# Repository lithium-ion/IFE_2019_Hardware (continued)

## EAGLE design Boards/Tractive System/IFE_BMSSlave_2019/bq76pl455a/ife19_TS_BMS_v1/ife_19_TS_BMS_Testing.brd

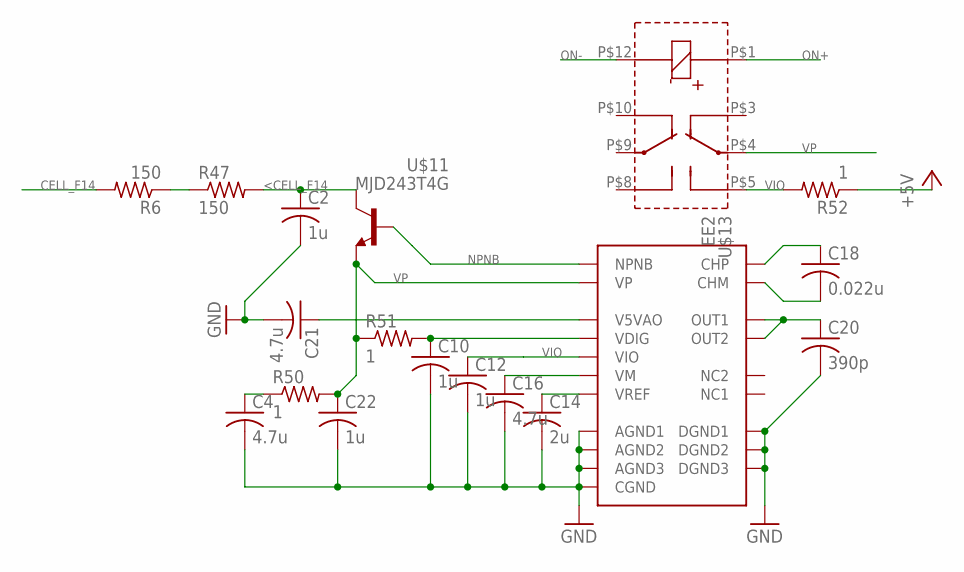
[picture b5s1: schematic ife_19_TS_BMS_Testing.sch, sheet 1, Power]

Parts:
C2, C10, C12, C22: 1u; C0805
C4, C16, C21: 4.7u; C0805
C14: 2u; C0805
C18: 0.022u; C0805
C20: 390p; C0805
R6, R47: 150; R2512
R50, R51, R52: 1; R0805
U$1: BQ76PL455A; TQFP80
U$11: MJD243T4G; TO252
U$13: EE2; EE2-DPDT-SMD

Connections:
<CELL_F14: C2.1, R47.2, U$11.4 (C)
CELL_F14: R6.2; also elsewhere on the board
GND: C2.2, C4.2, C10.2, C12.2, C14.2, C16.2, C20.2, C21.2, C22.2, U$1.30 (DGND1), U$1.35 (DGND2), U$1.37 (DGND3), U$1.48 (CGND), U$1.69 (AGND3), U$1.72 (AGND2), U$1.74 (AGND1); also elsewhere on the board
unnamed: C4.1, R50.1
unnamed: C10.1, R51.2, U$1.34 (VDIG)
unnamed: R52.2, U$13.P$5 ($P5)
unnamed: C14.1, U$1.67 (VREF)
unnamed: C16.1, U$1.31 (VM)
unnamed: C21.1, U$1.58 (V5VAO)
unnamed: R6.1, R47.1
unnamed: C18.1, U$1.32 (CHP)
unnamed: C18.2, U$1.33 (CHM)
unnamed: C20.1, U$1.68 (OUT2), U$1.73 (OUT1)
NPNB: U$1.71 (NPNB), U$11.1 (B)
ON+: U$13.P$1 ($P1); also elsewhere on the board
ON-: U$13.P$12 ($P12); also elsewhere on the board
VIO: C12.1, R52.1, U$1.41 (VIO); also elsewhere on the board
VP: C22.1, R50.2, R51.1, U$1.70 (VP), U$11.3 (E), U$13.P$4 ($P4)

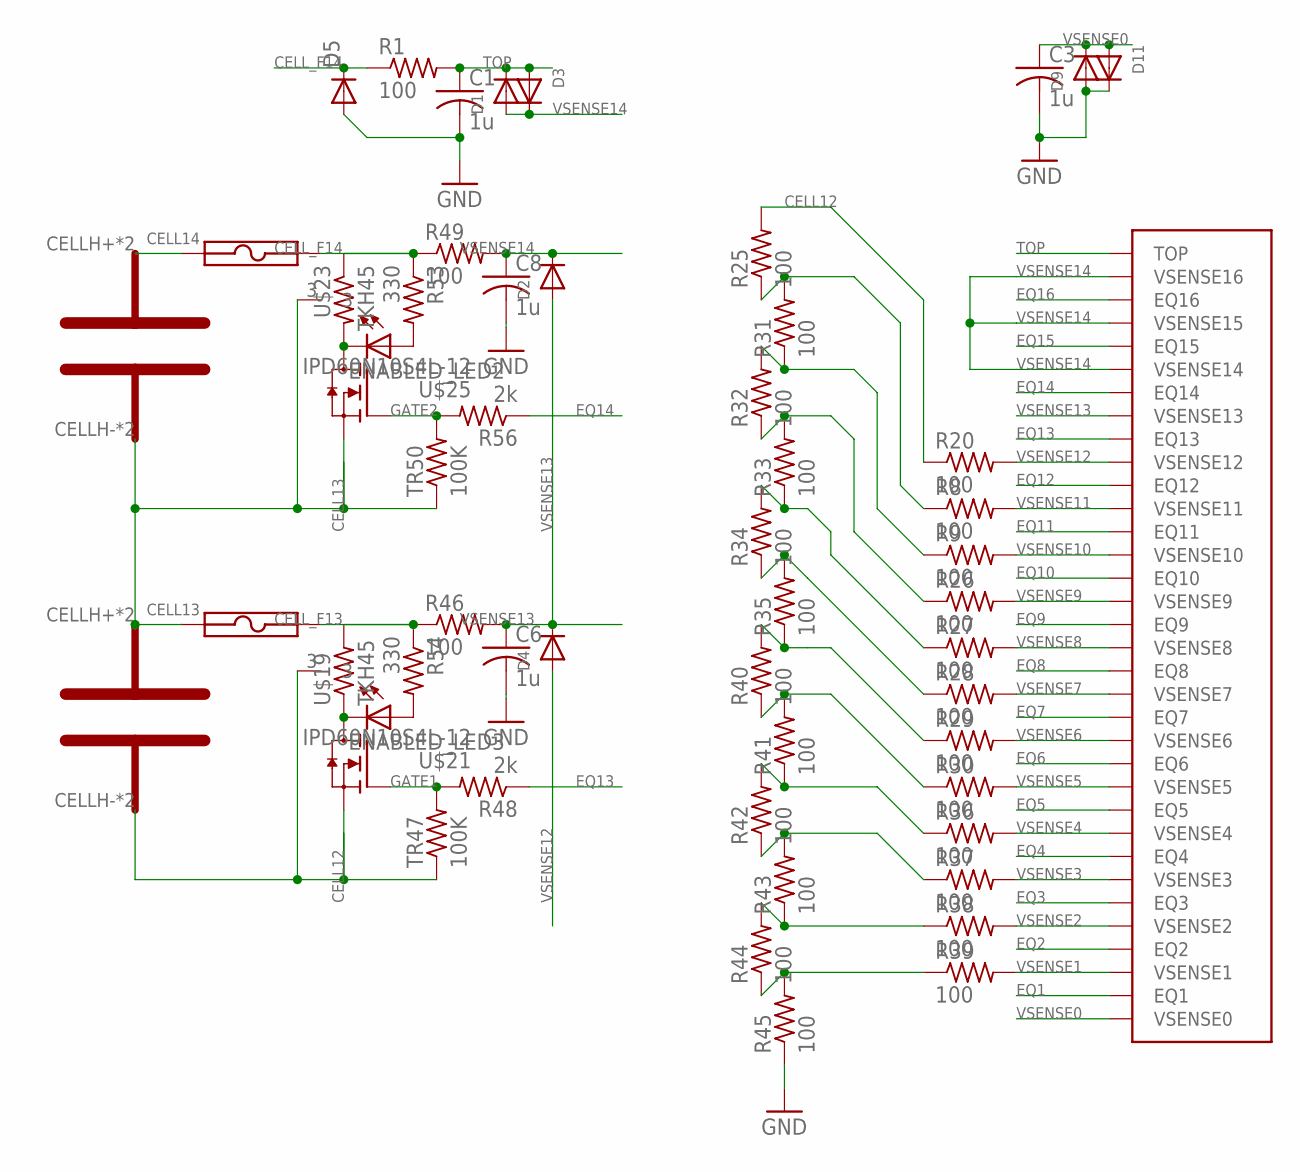
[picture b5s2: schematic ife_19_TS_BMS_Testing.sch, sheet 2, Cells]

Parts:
13, 14: LI6PT; 6PT
C1, C3, C6, C8: 1u; C0603K
D1, D2, D3, D4, D9, D11: DIODESOD-123; SOD-123
D5: DIODE-DO214AC; DO214AC
ENABLED_LED2, ENABLED_LED3: LEDCHIPLED_0603; CHIPLED_0603
R1, R8, R9, R20, R25, R26, R27, R28, R29, R30, R31, R32, R33, R34, R35, R36, R37, R38, R39, R40, R41, R42, R43, R44, R45, R46, R49: 100; R0603
R48, R56: 2k; R0603
R53, R54: 330; R0603
TR47, TR50: 100K; R0603
U$1: BQ76PL455A; TQFP80
U$18, U$22: SF-0603FP; 0603
U$19, U$23: TKH45; TO252-TKH-45
U$21, U$25: IPD60N10S4L-12; TO252

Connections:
CELL12: 13.CELLH- (CELL-), 13.CELLP- (CELL-), R20.1, R25.2, TR47.1, U$19.3, U$21.3 (S); also elsewhere on the board
CELL13: 13.CELLH+ (CELL+), 13.CELLP+ (CELL+), 14.CELLH- (CELL-), 14.CELLP- (CELL-), TR50.1, U$18.1, U$23.3, U$25.3 (S)
CELL14: 14.CELLH+ (CELL+), 14.CELLP+ (CELL+), U$22.1
CELL_F13: R46.1, R54.1, U$18.2, U$19.2; also elsewhere on the board
CELL_F14: D5.C, R1.1, R49.1, R53.1, U$22.2, U$23.1; also elsewhere on the board
EQ1: U$1.28 (EQ1)
EQ2: U$1.26 (EQ2)
EQ3: U$1.24 (EQ3)
EQ4: U$1.22 (EQ4)
EQ5: U$1.20 (EQ5)
EQ6: U$1.18 (EQ6)
EQ7: U$1.16 (EQ7)
EQ8: U$1.14 (EQ8)
EQ9: U$1.12 (EQ9)
EQ10: U$1.10 (EQ10)
EQ11: U$1.8 (EQ11)
EQ12: U$1.6 (EQ12)
EQ13: R48.1, U$1.4 (EQ13)
EQ14: R56.1, U$1.2 (EQ14)
EQ15: U$1.80 (EQ15)
EQ16: U$1.78 (EQ16)
GATE1: R48.2, TR47.2, U$21.1 (G)
GATE2: R56.2, TR50.2, U$25.1 (G)
GND: C1.2, C3.2, C6.2, C8.2, D5.A, D9.A, D11.C, R45.1; also elsewhere on the board
unnamed: ENABLED_LED2.A, R53.2
unnamed: ENABLED_LED3.A, R54.2
unnamed: ENABLED_LED3.C, U$19.1, U$21.2 (D)
unnamed: ENABLED_LED2.C, U$23.2, U$25.2 (D)
unnamed: R8.1, R25.1, R31.2
unnamed: R9.1, R31.1, R32.2
unnamed: R26.1, R32.1, R33.2
unnamed: R27.1, R33.1, R34.2
unnamed: R28.1, R34.1, R35.2
unnamed: R29.1, R35.1, R40.2
unnamed: R30.1, R40.1, R41.2
unnamed: R36.1, R41.1, R42.2
unnamed: R37.1, R42.1, R43.2
unnamed: R38.1, R43.1, R44.2
unnamed: R39.1, R44.1, R45.2
TOP: C1.1, D1.C, D3.A, R1.2, U$1.76 (TOP)
VSENSE0: C3.1, D9.C, D11.A, U$1.29 (VSENSE0)
VSENSE1: R39.2, U$1.27 (VSENSE1)
VSENSE2: R38.2, U$1.25 (VSENSE2)
VSENSE3: R37.2, U$1.23 (VSENSE3)
VSENSE4: R36.2, U$1.21 (VSENSE4)
VSENSE5: R30.2, U$1.19 (VSENSE5)
VSENSE6: R29.2, U$1.17 (VSENSE6)
VSENSE7: R28.2, U$1.15 (VSENSE7)
VSENSE8: R27.2, U$1.13 (VSENSE8)
VSENSE9: R26.2, U$1.11 (VSENSE9)
VSENSE10: R9.2, U$1.9 (VSENSE10)
VSENSE11: R8.2, U$1.7 (VSENSE11)
VSENSE12: D4.A, R20.2, U$1.5 (VSENSE12)
VSENSE13: C6.1, D2.A, D4.C, R46.2, U$1.3 (VSENSE13)
VSENSE14: C8.1, D1.A, D2.C, D3.C, R49.2, U$1.1 (VSENSE14), U$1.77 (VSENSE16), U$1.79 (VSENSE15)

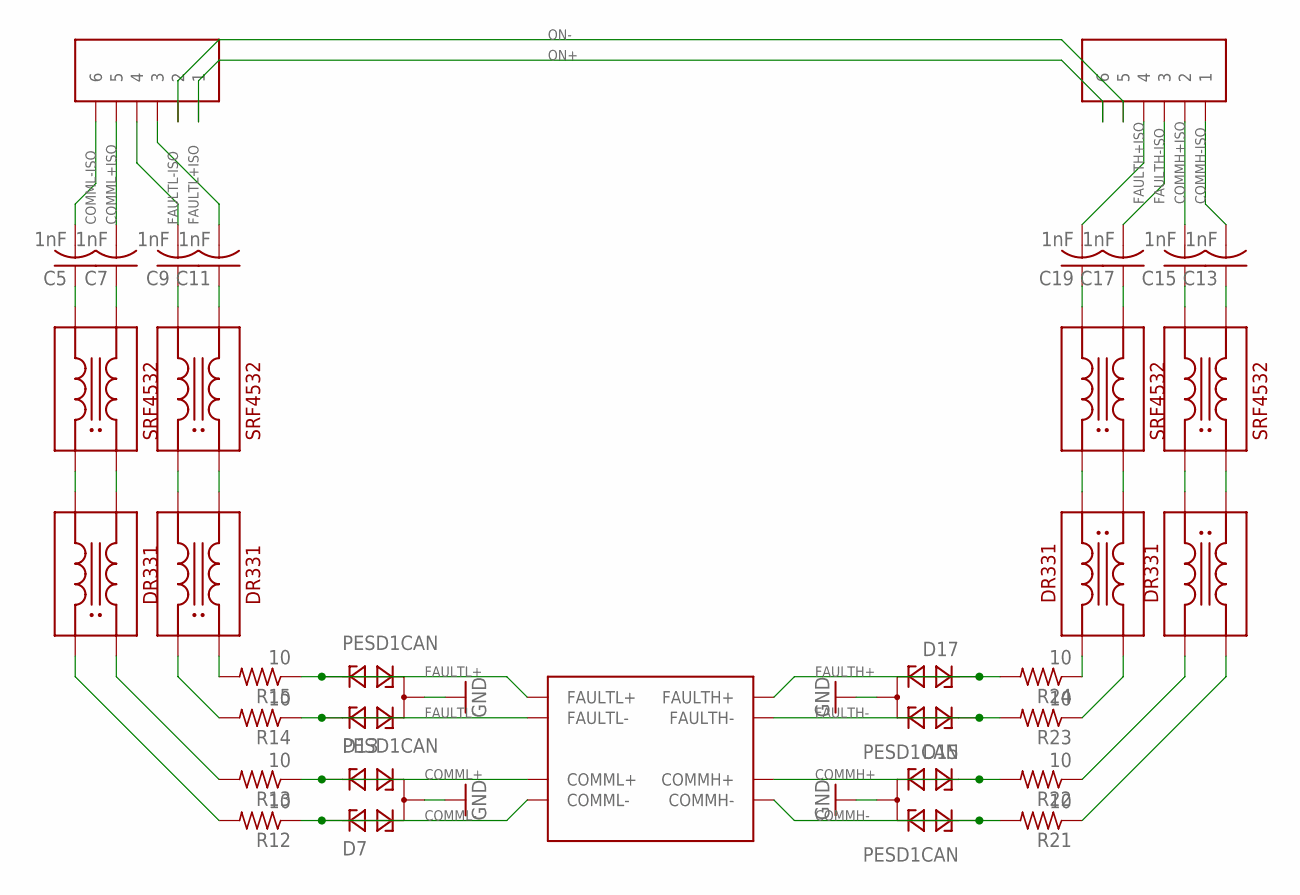
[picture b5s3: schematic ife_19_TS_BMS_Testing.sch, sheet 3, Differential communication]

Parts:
C5, C7, C9, C11, C13, C15, C17, C19: 1nF; C0805
D7, D13, D15, D17: PESD1CAN; SOT23
R12, R13, R14, R15, R21, R22, R23, R24: 10; R0805
U$1: BQ76PL455A; TQFP80
U$2, U$3, U$4, U$6: SRF5432
U$5, U$7: MICROFIT3.0-3P; 6POS-3MM
U$10, U$12, U$14, U$16: DR331

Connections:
COMMH+: D15.1, R22.2, U$1.55 (COMMH+)
COMMH+ISO: C15.2, U$7.P$2 (2)
COMMH-: D15.2, R21.2, U$1.54 (COMMH-)
COMMH-ISO: C13.2, U$7.P$1 (1)
COMML+: D7.2, R13.1, U$1.52 (COMML+)
COMML+ISO: C7.2, U$5.P$5 (5)
COMML-: D7.1, R12.1, U$1.53 (COMML-)
COMML-ISO: C5.2, U$5.P$6 (6)
FAULTH+: D17.1, R24.2, U$1.57 (FAULTH+)
FAULTH+ISO: C19.2, U$7.P$4 (4)
FAULTH-: D17.2, R23.2, U$1.56 (FAULTH-)
FAULTH-ISO: C17.2, U$7.P$3 (3)
FAULTL+: D13.2, R15.1, U$1.50 (FAULTL+)
FAULTL+ISO: C11.2, U$5.P$3 (3)
FAULTL-: D13.1, R14.1, U$1.51 (FAULTL-)
FAULTL-ISO: C9.2, U$5.P$4 (4)
GND: D7.3, D13.3, D15.3, D17.3; also elsewhere on the board
unnamed: C5.1, U$2.P$3 (3)
unnamed: C7.1, U$2.P$2 (2)
unnamed: C9.1, U$3.P$3 (3)
unnamed: C11.1, U$3.P$2 (2)
unnamed: C13.1, U$6.P$2 (2)
unnamed: C15.1, U$6.P$3 (3)
unnamed: C17.1, U$4.P$2 (2)
unnamed: C19.1, U$4.P$3 (3)
unnamed: U$6.P$4 (4), U$14.P$2 (2)
unnamed: U$6.P$1 (1), U$14.P$1 (1)
unnamed: U$4.P$4 (4), U$16.P$2 (2)
unnamed: U$4.P$1 (1), U$16.P$1 (1)
unnamed: U$2.P$1 (1), U$10.P$3 (3)
unnamed: U$2.P$4 (4), U$10.P$4 (4)
unnamed: U$3.P$1 (1), U$12.P$3 (3)
unnamed: U$3.P$4 (4), U$12.P$4 (4)
unnamed: R14.2, U$12.P$1 (1)
unnamed: R13.2, U$10.P$2 (2)
unnamed: R12.2, U$10.P$1 (1)
unnamed: R15.2, U$12.P$2 (2)
unnamed: R23.1, U$16.P$4 (4)
unnamed: R22.1, U$14.P$3 (3)
unnamed: R21.1, U$14.P$4 (4)
unnamed: R24.1, U$16.P$3 (3)
ON+: U$5.P$1 (1), U$7.P$6 (6); also elsewhere on the board
ON-: U$5.P$2 (2), U$7.P$5 (5); also elsewhere on the board

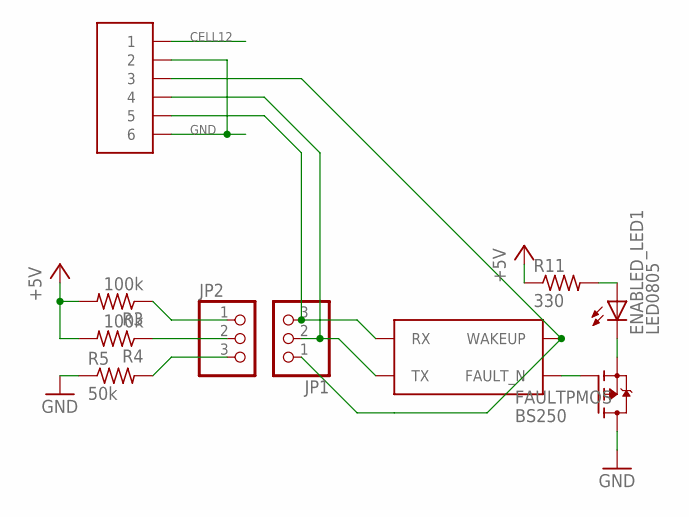
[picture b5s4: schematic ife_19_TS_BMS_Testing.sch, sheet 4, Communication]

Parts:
ENABLED_LED1: LED0805
FAULTPMOS: BS250; SOT23
JP1, JP2: PINHD-1X3CB; 1X03-CLEANBIG
R3, R4: 100k; R0805
R5: 50k; R0805
R11: 330; R0805
U$1: BQ76PL455A; TQFP80
U$9: MICROFIT3.0-3P; 6POS-3MM

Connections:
CELL12: U$9.P$1 (1); also elsewhere on the board
FAULT_N: FAULTPMOS.1 (G), U$1.40 (FAULT_N)
GND: FAULTPMOS.3 (D), R5.1, U$9.P$2 (2), U$9.P$6 (6); also elsewhere on the board
unnamed: ENABLED_LED1.2 (C), FAULTPMOS.2 (S)
unnamed: ENABLED_LED1.1 (A), R11.2
unnamed: JP2.1, R3.1
unnamed: JP1.3, U$1.39 (RX), U$9.P$5 (5)
unnamed: JP2.2, R4.1
unnamed: JP2.3, R5.2
unnamed: JP1.2, U$1.38 (TX), U$9.P$4 (4)
unnamed: JP1.1, U$1.49 (WAKEUP), U$9.P$3 (3)
VIO: R3.2, R4.2, R11.1; also elsewhere on the board

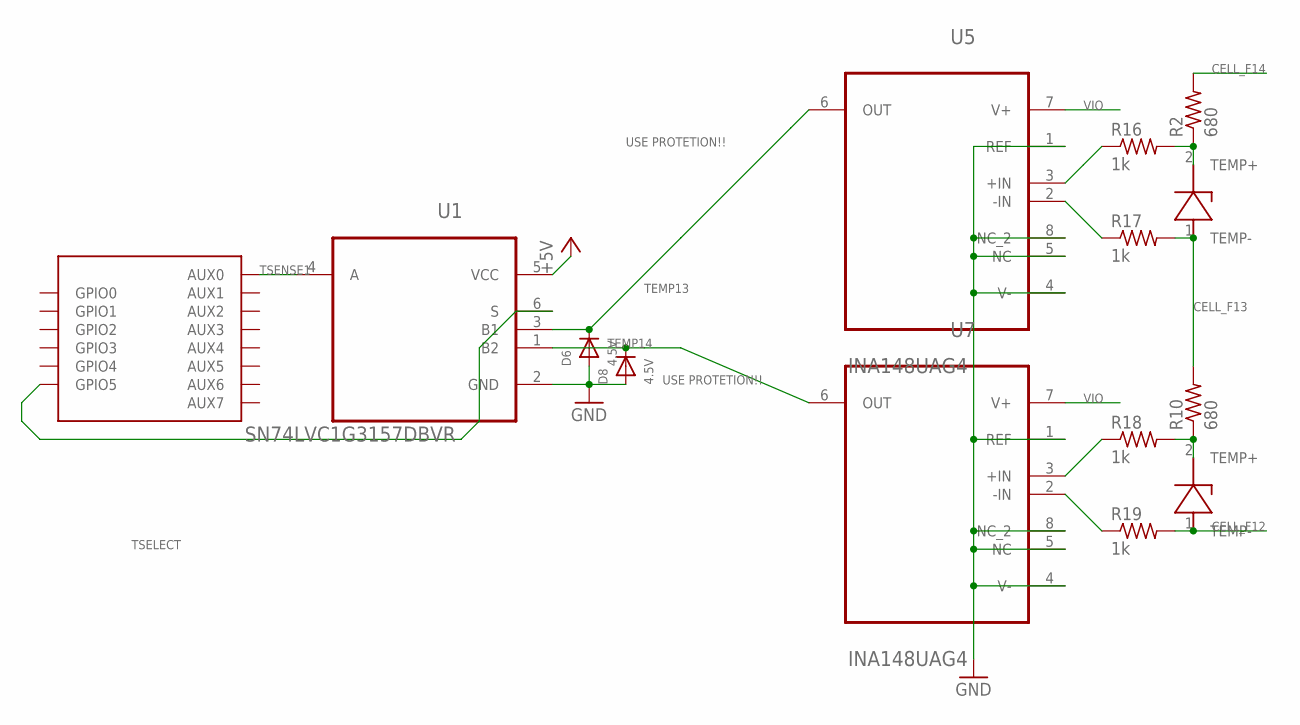
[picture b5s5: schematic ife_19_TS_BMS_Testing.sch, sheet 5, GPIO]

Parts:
13, 14: LI6PT; 6PT
D6, D8: 4.5V; SOD-123
R2, R10: 680; R0603
R16, R17, R18, R19: 1k; R0603
U1: SN74LVC1G3157DBVR; SOT95P280X145-6N
U5, U7: INA148UAG4; SOIC127P600X175-8N
U$1: BQ76PL455A; TQFP80

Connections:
CELL_F12: 13.1 (TEMP-), R19.2
CELL_F13: 14.1 (TEMP-), R10.2, R17.2; also elsewhere on the board
CELL_F14: R2.2; also elsewhere on the board
GND: D6.A, D8.A, U1.2 (GND), U5.1 (REF), U5.4 (V-), U5.5 (NC), U5.8 (NC_2), U7.1 (REF), U7.4 (V-), U7.5 (NC), U7.8 (NC_2); also elsewhere on the board
unnamed: R16.1, U5.3 (+IN)
unnamed: R18.1, U7.3 (+IN)
unnamed: R17.1, U5.2 (-IN)
unnamed: 14.2 (TEMP+), R2.1, R16.2
unnamed: 13.2 (TEMP+), R10.1, R18.2
unnamed: R19.1, U7.2 (-IN)
TEMP13: D6.C, U1.3 (B1), U5.6 (OUT)
TEMP14: D8.C, U1.1 (B2), U7.6 (OUT)
TSELECT: U1.6 (S), U$1.42 (GPIO5)
TSENSE1: U1.4 (A), U$1.66 (AUX0)
VIO: U1.5 (VCC), U5.7 (V+), U7.7 (V+); also elsewhere on the board

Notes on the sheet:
USE PROTETION!!

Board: 4 copper layers, 122 parts (58 on the bottom side), 117 nets, no tracks yet.

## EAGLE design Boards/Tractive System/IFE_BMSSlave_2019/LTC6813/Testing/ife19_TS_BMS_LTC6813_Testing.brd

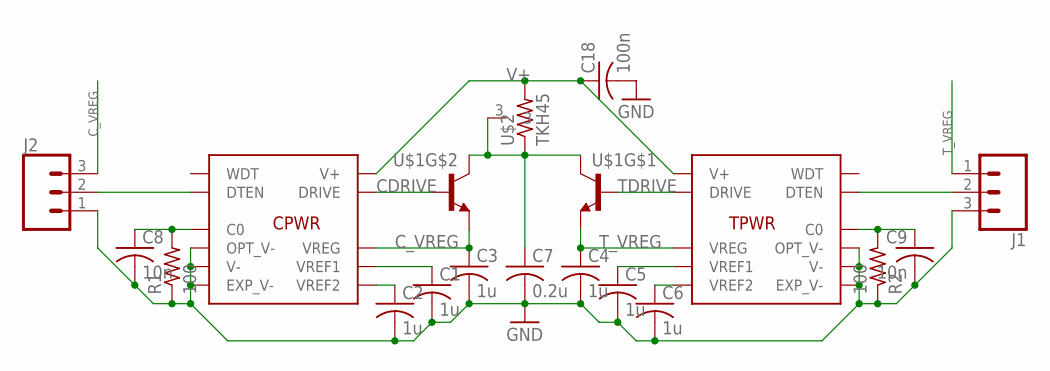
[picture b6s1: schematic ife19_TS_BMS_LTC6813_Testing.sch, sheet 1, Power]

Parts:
C: LTC6813-1; HTQFP-64-EXP
C1, C2, C3, C4, C5, C6: 1u; C0603
C7: 0.2u; C1206
C8, C9: 10n; C0603
C18: 100n; C0603
J1, J2: CONN_03; 1X03
R1, R2: 100; R0603
T: LTC6813-1; HTQFP-64-EXP
U$1: PHPT610030NK; LFPAK56D
U$2: TKH45; TO252-TKH-45

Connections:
CDRIVE: C.49 (DRIVE), U$1.B2 (B)
C_VREG: C.48 (VREG), C3.1, J2.3, U$1.E2 (E); also elsewhere on the board
GND: C.59 (V-), C.60 (OPT_V-), C.65 (EXP_V-), C1.2, C2.2, C3.2, C4.2, C5.2, C6.2, C7.2, C8.2, C9.2, C18.2, J1.3, J2.1, R1.1, R2.1, T.59 (V-), T.60 (OPT_V-), T.65 (EXP_V-); also elsewhere on the board
unnamed: C.51 (VREF1), C1.1
unnamed: C.50 (VREF2), C2.1
unnamed: C5.1, T.51 (VREF1)
unnamed: C6.1, T.50 (VREF2)
unnamed: C.38 (C0), C8.1, R1.2
unnamed: C7.1, U$1.C1 (C), U$1.C2 (C), U$2.1, U$2.3
unnamed: C9.1, R2.2, T.38 (C0)
unnamed: J1.2, T.52 (DTEN)
unnamed: C.52 (DTEN), J2.2
TDRIVE: T.49 (DRIVE), U$1.B1 (B)
T_VREG: C4.1, J1.1, T.48 (VREG), U$1.E1 (E); also elsewhere on the board
V+: C.1 (V+), C18.1, T.1 (V+), U$2.2

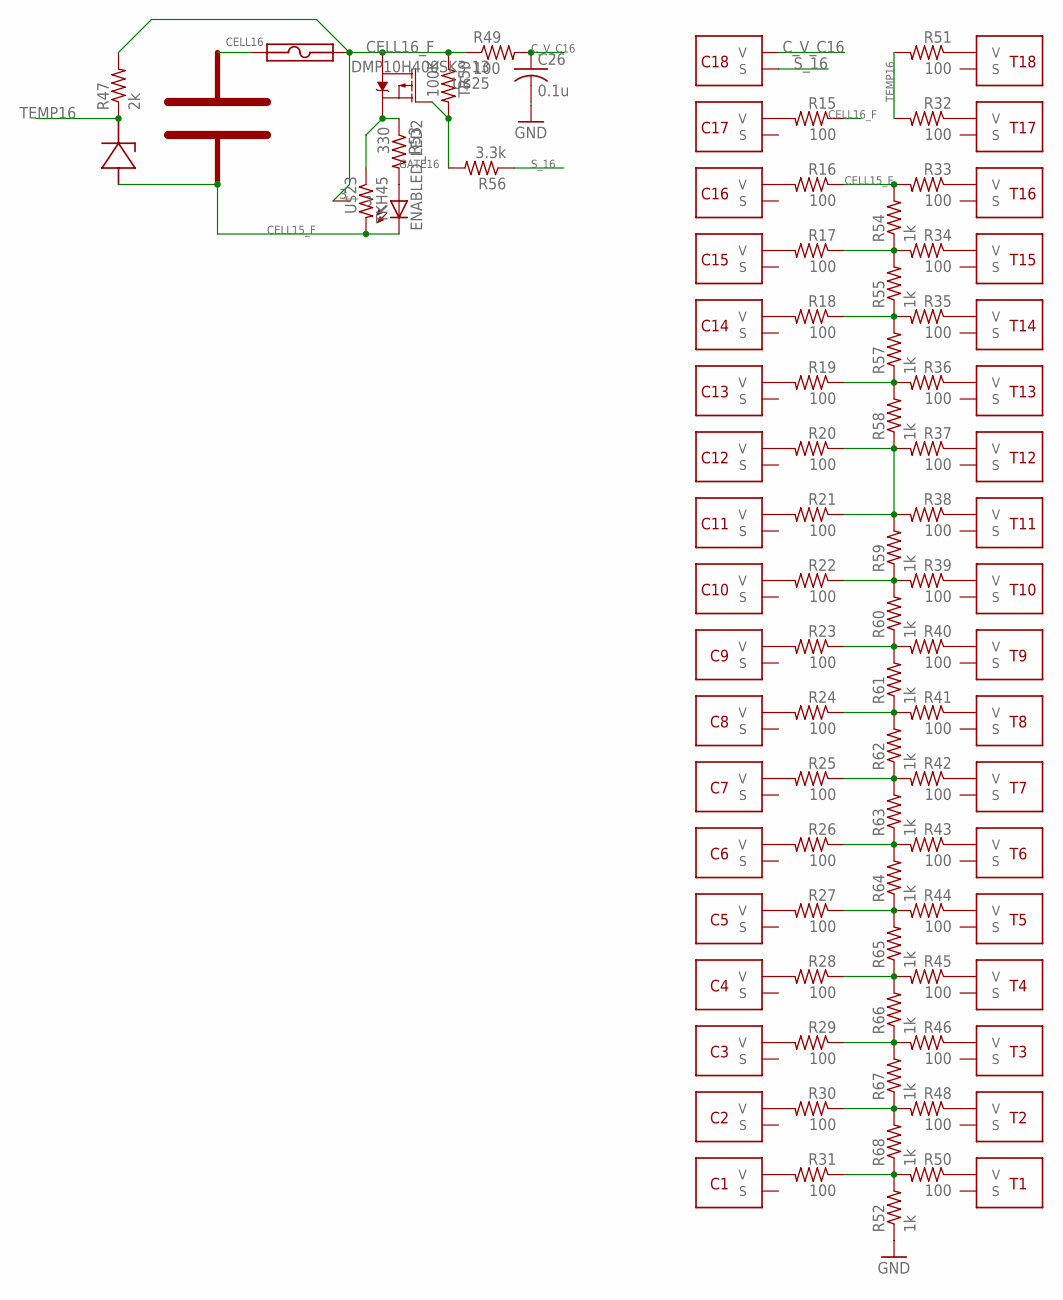
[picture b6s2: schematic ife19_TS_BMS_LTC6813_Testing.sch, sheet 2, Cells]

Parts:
C: LTC6813-1; HTQFP-64-EXP
C26: 0.1u; C0603K
ENABLED_LED2: LEDCHIPLED_0603; CHIPLED_0603
R15, R16, R17, R18, R19, R20, R21, R22, R23, R24, R25, R26, R27, R28, R29, R30, R31, R32, R33, R34, R35, R36, R37, R38, R39, R40, R41, R42, R43, R44, R45, R46, R48, R49, R50, R51: 100; R0603
R47: 2k; R0603
R52, R54, R55, R57, R58, R59, R60, R61, R62, R63, R64, R65, R66, R67, R68: 1k; R0603
R53: 330; R0603
R56: 3.3k; R0603
T: LTC6813-1; HTQFP-64-EXP
TR50: 100K; R0603
U$6: LI6PT; 6PT
U$22: 04661206; R1206W
U$23: TKH45; TO252-TKH-45
U$25: DMP10H400SK3-13; TO252

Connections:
CELL15_F: ENABLED_LED2.C, R16.1, R33.2, R54.2, U$6.1 (TEMP-), U$6.CELLH- (CELL-), U$6.CELLP- (CELL-), U$23.2
CELL16: U$6.CELLH+ (CELL+), U$6.CELLP+ (CELL+), U$22.1
CELL16_F: R15.1, R47.2, R49.1, TR50.1, U$22.2, U$23.3, U$25.2 (D)
C_V_C16: C.2 (V), C26.1, R49.2
GATE16: R56.2, TR50.2, U$25.1 (G)
GND: C26.2, R52.1; also elsewhere on the board
unnamed: ENABLED_LED2.A, R53.2
unnamed: C.4 (V), R15.2
unnamed: C.6 (V), R16.2
unnamed: C.8 (V), R17.2
unnamed: C.10 (V), R18.2
unnamed: C.12 (V), R19.2
unnamed: C.14 (V), R20.2
unnamed: C.16 (V), R21.2
unnamed: C.18 (V), R22.2
unnamed: C.20 (V), R23.2
unnamed: C.22 (V), R24.2
unnamed: C.24 (V), R25.2
unnamed: C.26 (V), R26.2
unnamed: C.28 (V), R27.2
unnamed: C.30 (V), R28.2
unnamed: C.32 (V), R29.2
unnamed: C.34 (V), R30.2
unnamed: C.36 (V), R31.2
unnamed: R32.1, T.4 (V)
unnamed: R33.1, T.6 (V)
unnamed: R34.1, T.8 (V)
unnamed: R35.1, T.10 (V)
unnamed: R36.1, T.12 (V)
unnamed: R37.1, T.14 (V)
unnamed: R38.1, T.16 (V)
unnamed: R39.1, T.18 (V)
unnamed: R40.1, T.20 (V)
unnamed: R41.1, T.22 (V)
unnamed: R42.1, T.24 (V)
unnamed: R43.1, T.26 (V)
unnamed: R44.1, T.28 (V)
unnamed: R45.1, T.30 (V)
unnamed: R46.1, T.32 (V)
unnamed: R48.1, T.34 (V)
unnamed: R50.1, T.36 (V)
unnamed: R51.1, T.2 (V)
unnamed: R20.1, R21.1, R37.2, R38.2, R58.1, R59.2
unnamed: R17.1, R34.2, R54.1, R55.2
unnamed: R18.1, R35.2, R55.1, R57.2
unnamed: R19.1, R36.2, R57.1, R58.2
unnamed: R22.1, R39.2, R59.1, R60.2
unnamed: R23.1, R40.2, R60.1, R61.2
unnamed: R24.1, R41.2, R61.1, R62.2
unnamed: R25.1, R42.2, R62.1, R63.2
unnamed: R26.1, R43.2, R63.1, R64.2
unnamed: R27.1, R44.2, R64.1, R65.2
unnamed: R28.1, R45.2, R65.1, R66.2
unnamed: R29.1, R46.2, R66.1, R67.2
unnamed: R30.1, R48.2, R67.1, R68.2
unnamed: R31.1, R50.2, R52.2, R68.1
unnamed: R53.1, U$23.1, U$25.3 (S)
S_16: C.3 (S), R56.1
TEMP16: R32.2, R47.1, R51.2, U$6.2 (TEMP+)

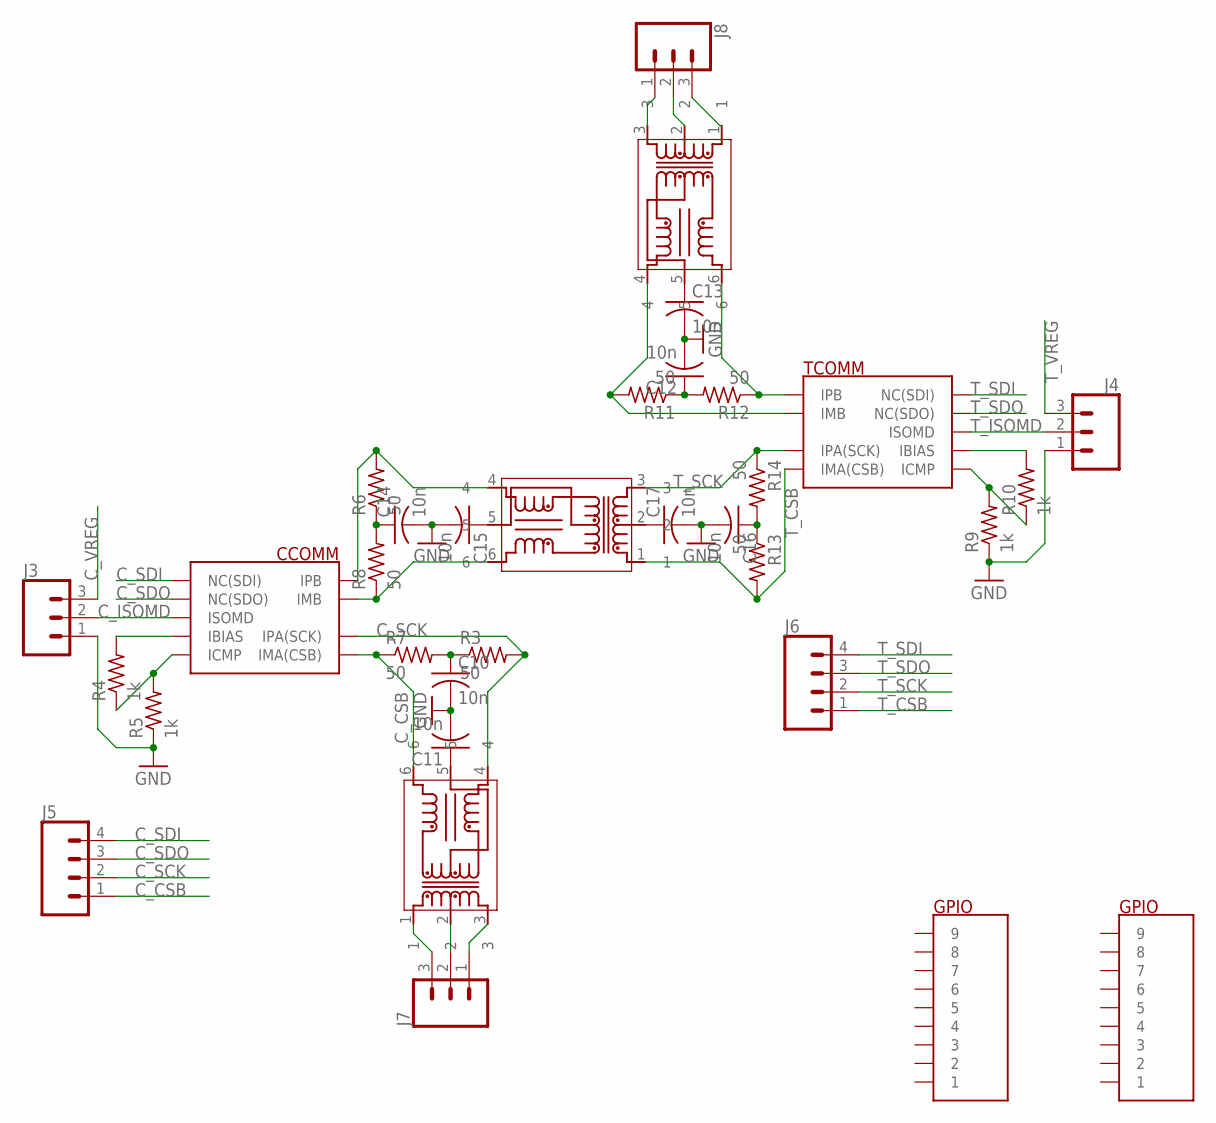
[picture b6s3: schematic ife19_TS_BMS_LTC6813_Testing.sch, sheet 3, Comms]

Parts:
C: LTC6813-1; HTQFP-64-EXP
C10, C11, C12, C13, C14, C15, C16, C17: 10n; C0603K
J3, J4, J7, J8: CONN_03; 1X03
J5, J6: CONN_04; 1X04
R3, R6, R7, R8, R11, R12, R13, R14: 50; R0603
R4, R5, R9, R10: 1k; R0603
T: LTC6813-1; HTQFP-64-EXP
U$3, U$4, U$5: HM2108NL

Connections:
C_CSB: C.61 (IMA(CSB)), J5.1, R7.1, U$3.6
C_ISOMD: C.55 (ISOMD), J3.2
C_SCK: C.62 (IPA(SCK)), J5.2, R3.2, U$3.4
C_SDI: C.53 (NC(SDI)), J5.4
C_SDO: C.54 (NC(SDO)), J5.3
C_VREG: J3.3; also elsewhere on the board
GND: C10.2, C11.2, C12.2, C13.2, C14.2, C15.2, C16.2, C17.2, J3.1, J4.1, R5.1, R9.1; also elsewhere on the board
unnamed: C.58 (ICMP), R4.1, R5.2
unnamed: C.57 (IBIAS), R4.2
unnamed: R10.2, T.57 (IBIAS)
unnamed: R9.2, R10.1, T.58 (ICMP)
unnamed: C10.1, R3.1, R7.2
unnamed: C11.1, U$3.5
unnamed: C12.1, R11.1, R12.2
unnamed: C13.1, U$4.5
unnamed: R11.2, T.63 (IMB), U$4.4
unnamed: R12.1, T.64 (IPB), U$4.6
unnamed: C14.1, R6.1, R8.2
unnamed: C15.1, U$5.5
unnamed: C.64 (IPB), R6.2, U$5.4
unnamed: C.63 (IMB), R8.1, U$5.6
unnamed: C16.1, R13.1, R14.2
unnamed: C17.1, U$5.2
unnamed: J8.1, U$4.3
unnamed: J8.2, U$4.2
unnamed: J8.3, U$4.1
unnamed: J7.2, U$3.2
unnamed: J7.3, U$3.1
unnamed: J7.1, U$3.3
T_CSB: J6.1, R13.2, T.61 (IMA(CSB)), U$5.1
T_ISOMD: J4.2, T.55 (ISOMD)
T_SCK: J6.2, R14.1, T.62 (IPA(SCK)), U$5.3
T_SDI: J6.4, T.53 (NC(SDI))
T_SDO: J6.3, T.54 (NC(SDO))
T_VREG: J4.3; also elsewhere on the board

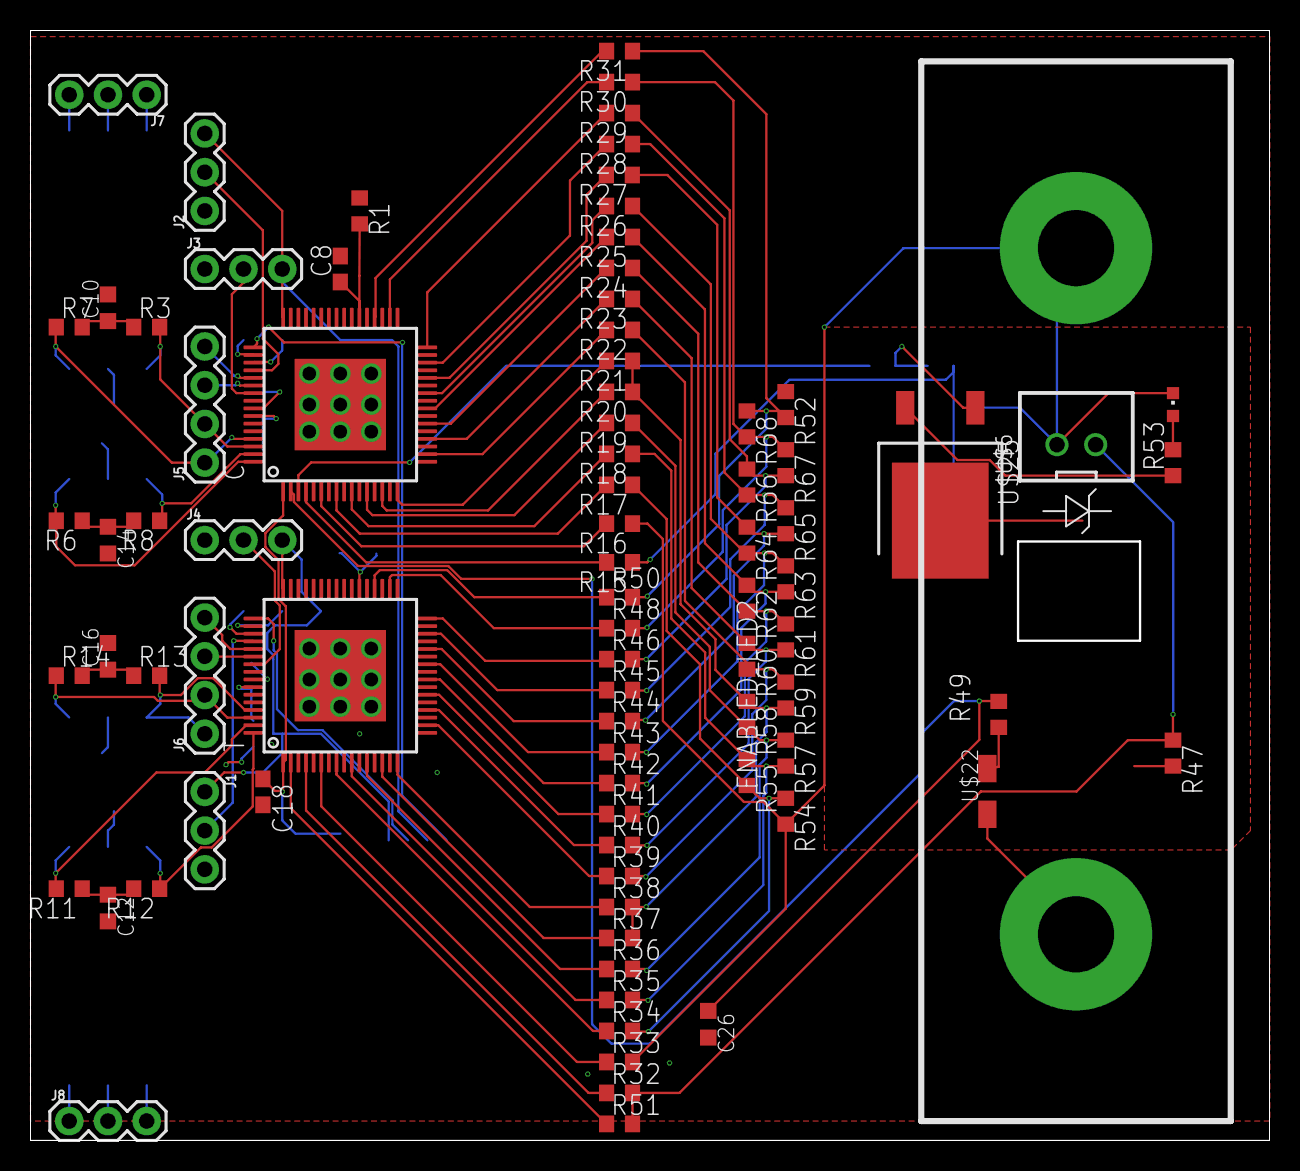
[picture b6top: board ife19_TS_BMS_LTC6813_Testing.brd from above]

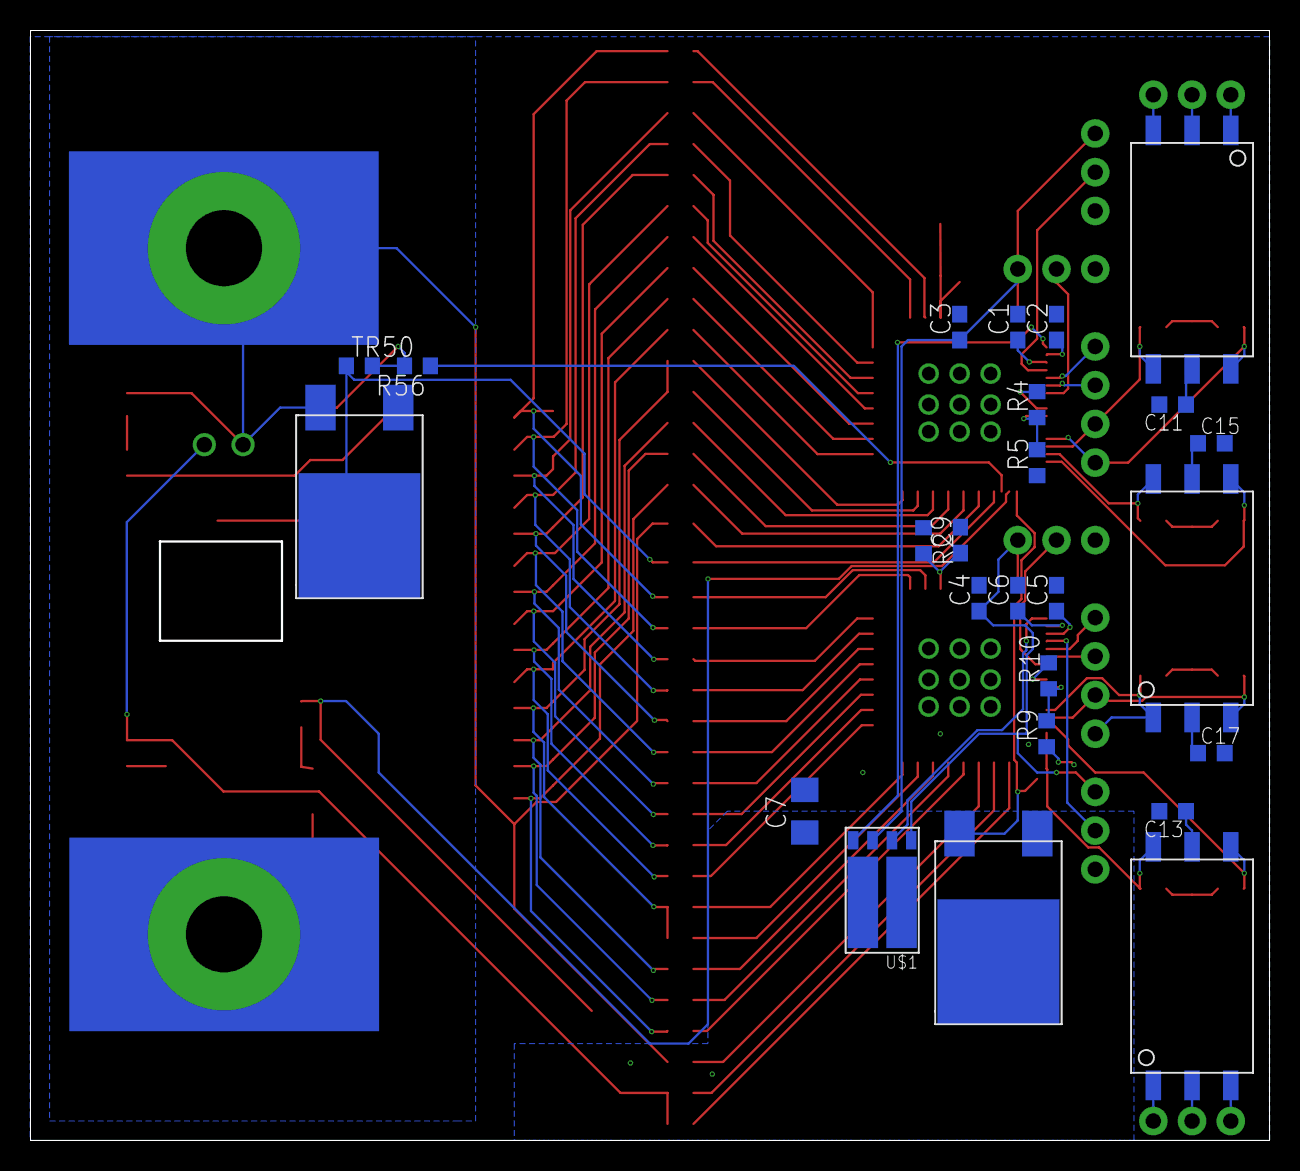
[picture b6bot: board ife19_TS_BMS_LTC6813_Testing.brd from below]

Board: 2 copper layers, 81.1 x 72.6 mm, 108 parts (25 on the bottom side), 105 nets.

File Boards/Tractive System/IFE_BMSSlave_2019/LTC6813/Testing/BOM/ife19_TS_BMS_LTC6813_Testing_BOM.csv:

Qty,Value,Device,Parts
1,SF-0603FP,04661.25NRHF,U$22
6,1u,885012106022,"C1, C2, C3, C4, C5, C6"
2,0.1u,CC0603KRX7R0BB104,"C18, C26"
10,10n,CC0603KRX7R0BB103,"C8, C9, C10, C11, C12, C13, C14, C15, C16, C17"
1,0.2u,VJ1206Y274KXBAT,C7
1,IPD60N10S4L-12,DMP10H400SK3-13,U$25
3,HM2108NL,HM2108NL,"U$3, U$4, U$5"
1,PHPT610030NK,PHPT610030NKX,U$1
19,1k,RC0603FR-071KL,"R4, R5, R9, R10, R52, R54, R55, R57, R58, R59, R60, R61, R62, R63, R64, R65, R66, R67, R68"
1,2k,RC0603FR-102KL,R47
1,3.3k,RC0603JR-073K3L,R56
8,50,RC0603FR-0749R9L,"R3, R6, R7, R8, R11, R12, R13, R14"
1,100K,RCA0603100KJNEC,TR50
1,330,CRCW0603330RJNEAC,R53
1,TKH45,TKH45P5R00FE-TR,U$23
1,TKH45,TKH45P300RFE-TR,U$2

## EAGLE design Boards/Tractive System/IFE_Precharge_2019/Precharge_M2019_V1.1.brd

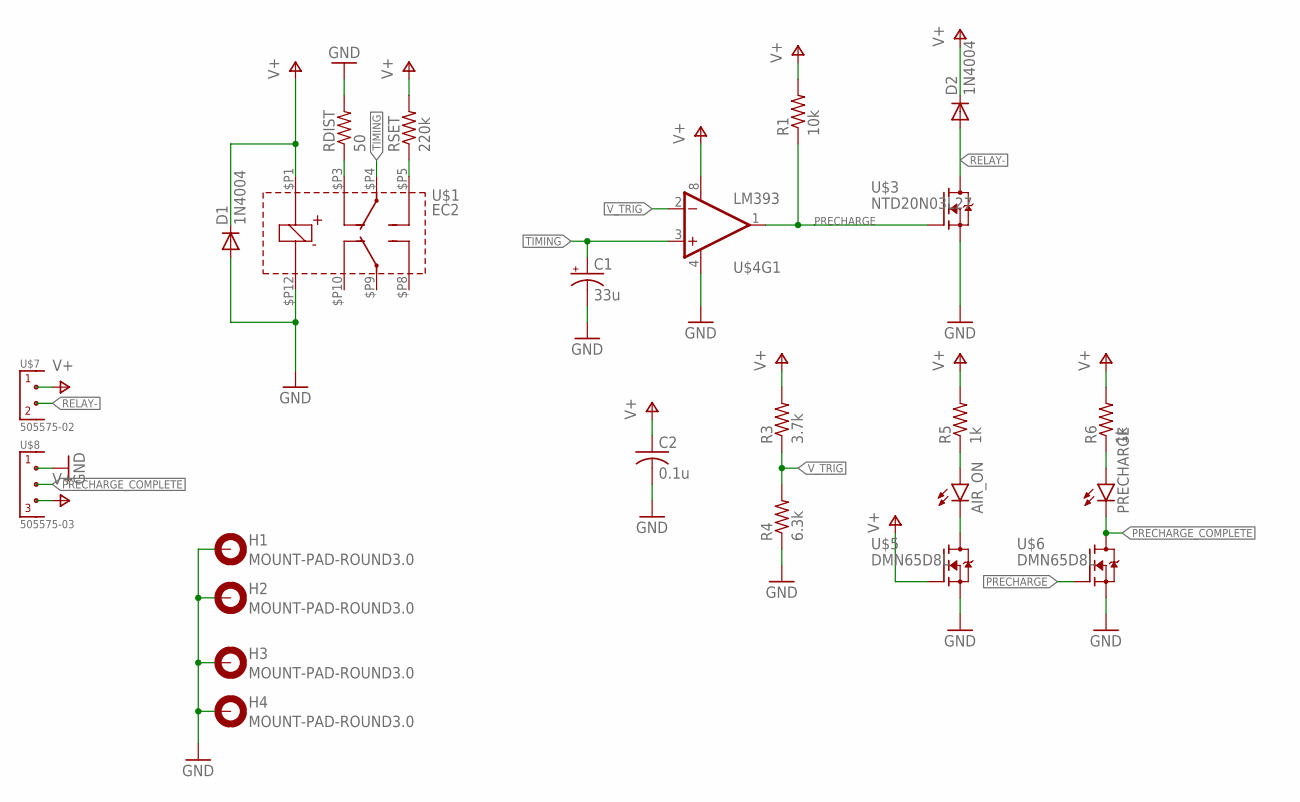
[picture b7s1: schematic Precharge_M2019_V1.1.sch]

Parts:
AIR_ON: LED0603; LED-0603
C1: 33u; E2,5-5
C2: 0.1u; C0805
D1, D2: 1N4004; DO41-10
H1, H2, H3, H4: MOUNT-PAD-ROUND3.0; 3,0-PAD
PRECHARGE: LED0603; LED-0603
R1: 10k; R0805
R3: 3.7k; R0805
R4: 6.3k; R0805
R5, R6: 1k; R0805
RDIST: 50; AXIAL-0.5
RSET: 220k; 0207/10
U$1: EC2; DPDT_2.54
U$3: NTD20N03L27; DPACK
U$4: LM393; SO08
U$5, U$6: DMN65D8L; SOT23
U$7: 505575-02
U$8: 505575-03

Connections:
GND: C1.-, C2.2, D1.A, H1.B3,0, H2.B3,0, H3.B3,0, H4.B3,0, R4.1, RDIST.P$2 (2), U$1.$P12, U$3.3 (S), U$4.4 (V-), U$5.2 (S), U$6.2 (S), U$8.1
unnamed: RSET.1, U$1.$P5
unnamed: RDIST.P$1 (1), U$1.$P3
unnamed: AIR_ON.A, R5.1
unnamed: PRECHARGE.A, R6.1
unnamed: AIR_ON.C, U$5.3 (D)
PRECHARGE: R1.1, U$3.1 (G), U$4.1 (OUT), U$6.1 (G)
PRECHARGE_COMPLETE: PRECHARGE.C, U$6.3 (D), U$8.2
RELAY-: D2.A, U$3.2 (D), U$7.2
TIMING: C1.+, U$1.$P4, U$4.3 (+IN)
V+: C2.1, D1.C, D2.C, R1.2, R3.2, R5.2, R6.2, RSET.2, U$1.$P1, U$4.8 (V+), U$5.1 (G), U$7.1, U$8.3
V_TRIG: R3.1, R4.2, U$4.2 (-IN)

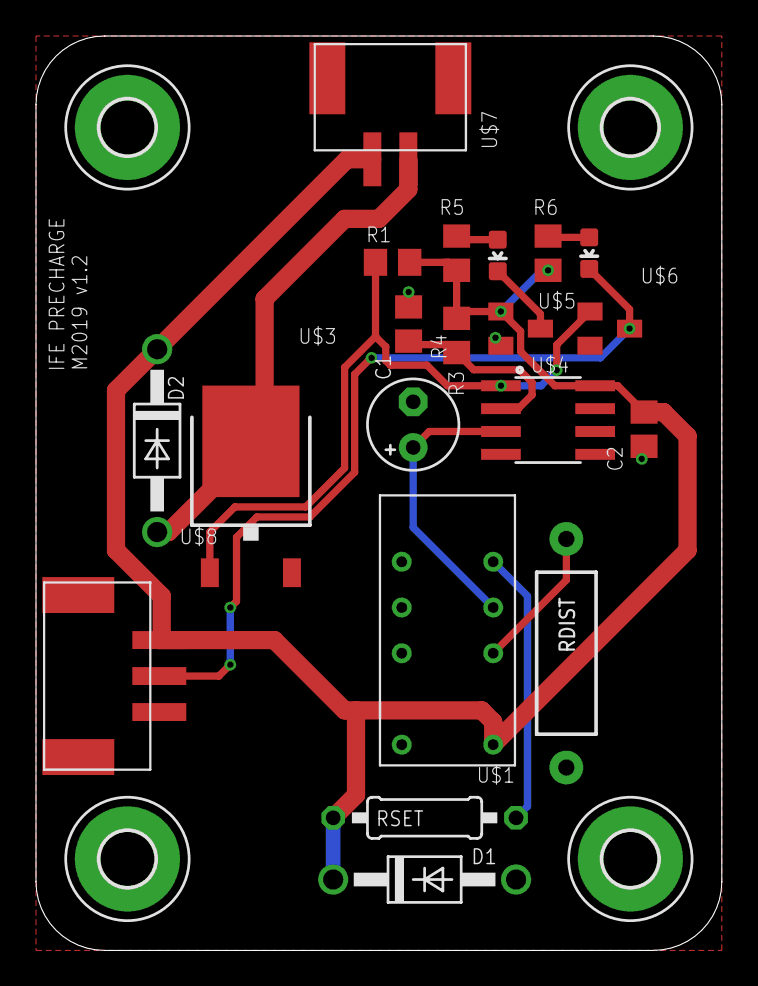
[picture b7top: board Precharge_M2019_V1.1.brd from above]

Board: 2 copper layers, 38.1 x 50.8 mm, 24 parts (0 on the bottom side), 12 nets.

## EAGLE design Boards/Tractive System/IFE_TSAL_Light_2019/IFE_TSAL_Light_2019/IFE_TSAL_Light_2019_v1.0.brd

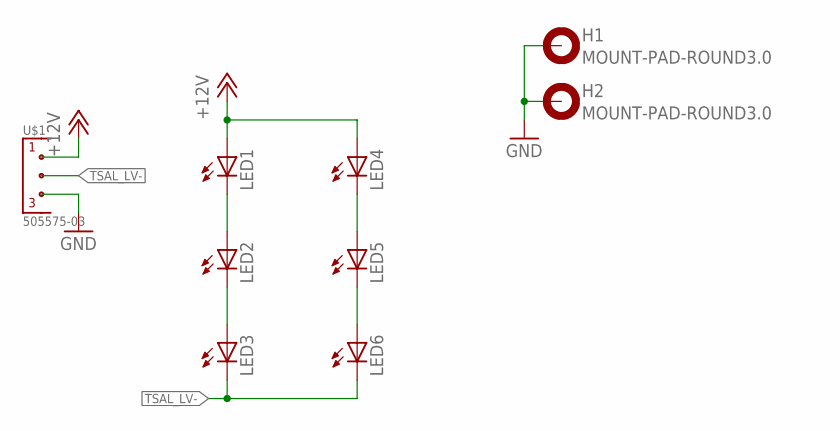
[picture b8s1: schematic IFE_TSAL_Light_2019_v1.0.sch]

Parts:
H1, H2: MOUNT-PAD-ROUND3.0; 3,0-PAD
LED1, LED2, LED3, LED4, LED5, LED6: LED5MM
U$1: 505575-03

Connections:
+12V: LED1.A, LED4.A, U$1.1
GND: H1.B3,0, H2.B3,0, U$1.3
unnamed: LED1.K (C), LED2.A
unnamed: LED2.K (C), LED3.A
unnamed: LED4.K (C), LED5.A
unnamed: LED5.K (C), LED6.A
TSAL_LV-: LED3.K (C), LED6.K (C), U$1.2

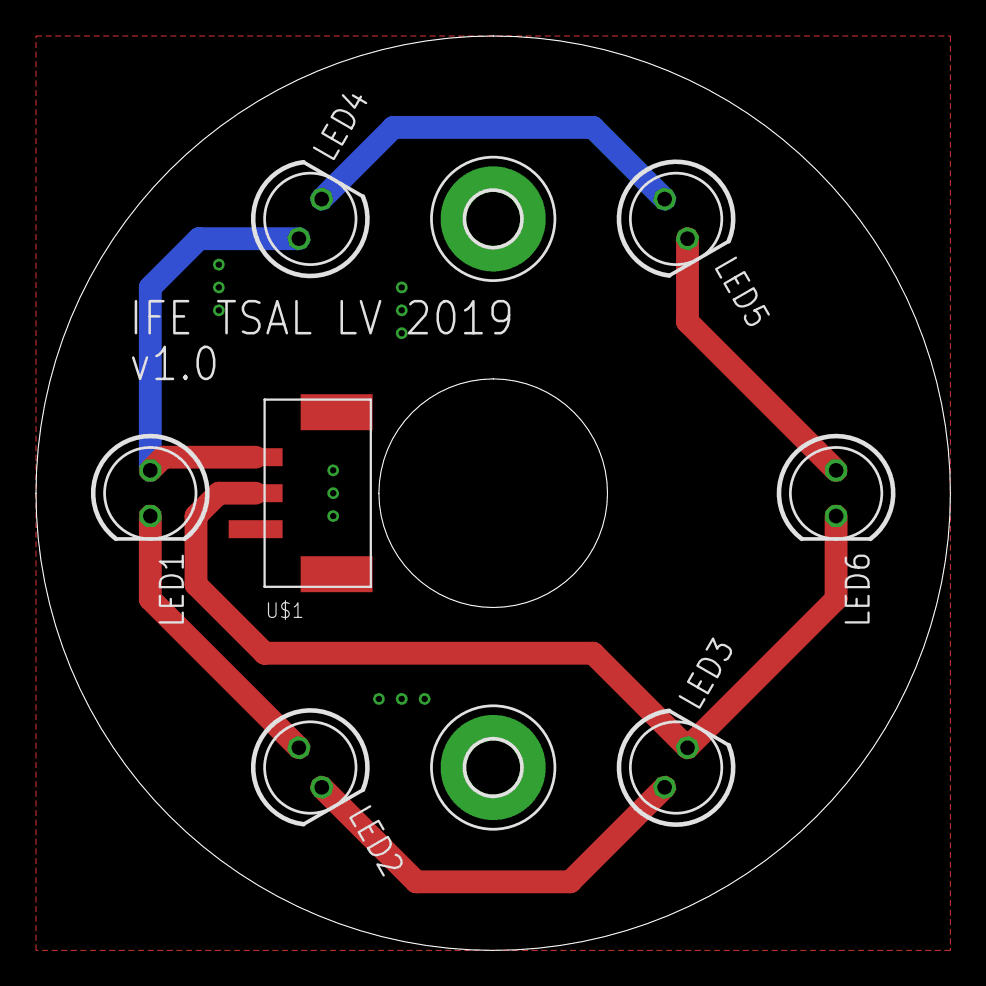
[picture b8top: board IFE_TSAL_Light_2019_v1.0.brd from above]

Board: 2 copper layers, 50.8 x 50.8 mm, 9 parts (0 on the bottom side), 7 nets.
